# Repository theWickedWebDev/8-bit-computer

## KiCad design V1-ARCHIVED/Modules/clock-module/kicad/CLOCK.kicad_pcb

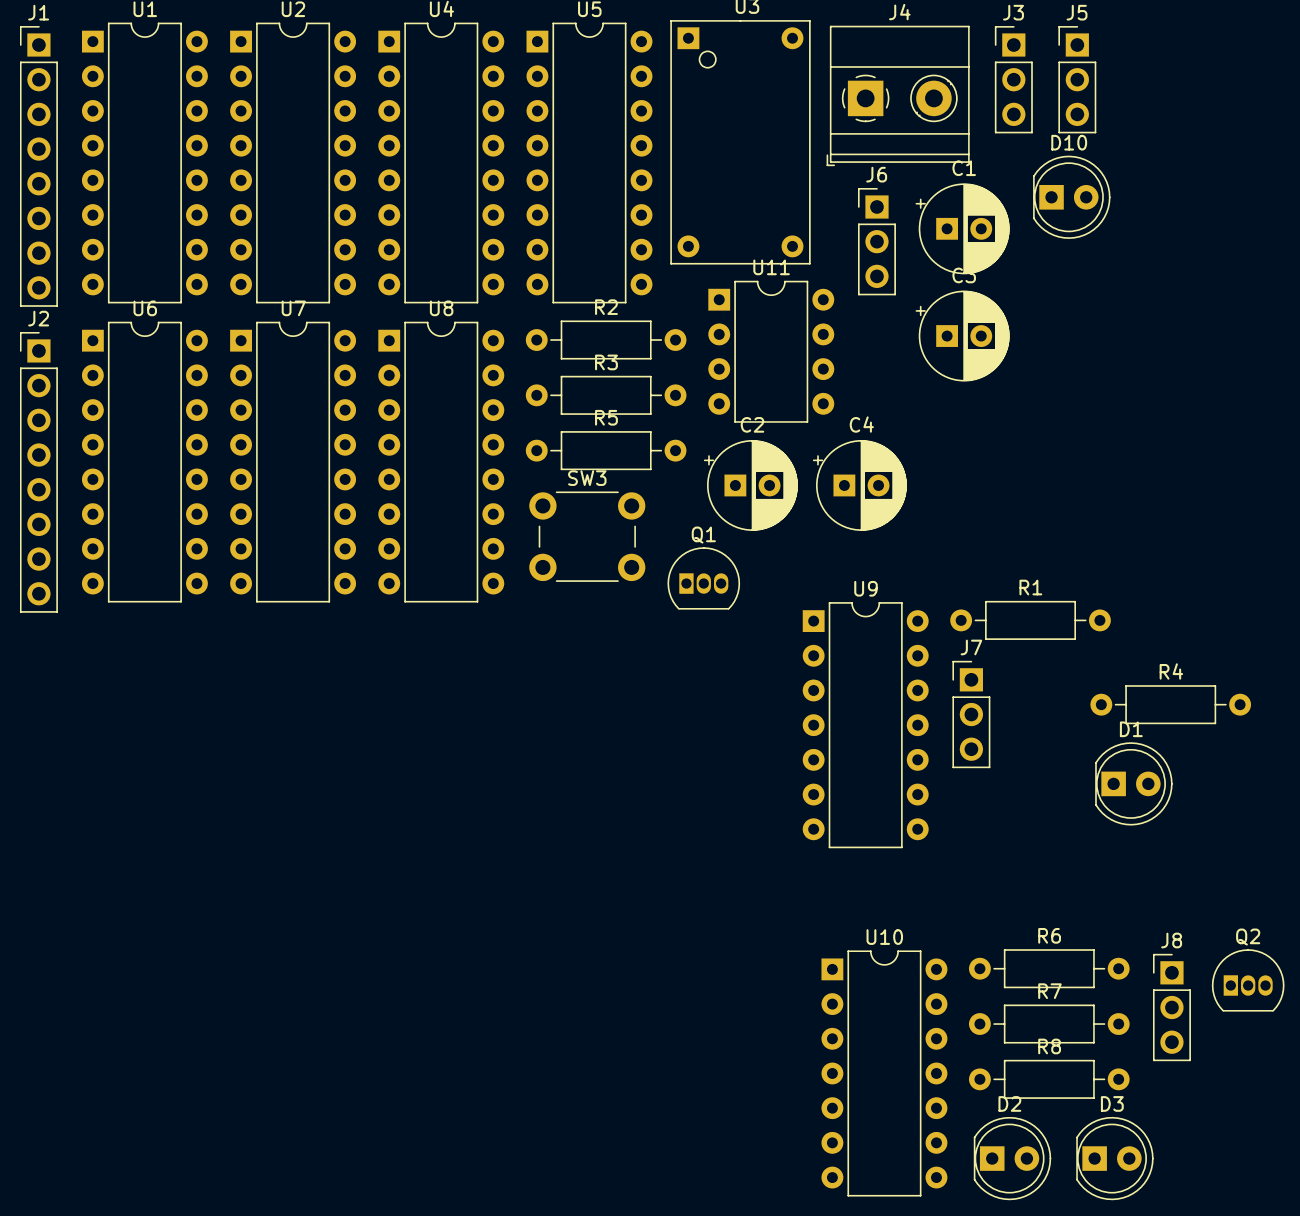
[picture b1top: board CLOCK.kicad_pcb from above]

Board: 4 copper layers, 38 parts (0 on the bottom side), 36 nets, no tracks yet.

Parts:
C1, C2, C3, C4: CP1; CP_Radial_D6.3mm_P2.50mm
D1, D2, D3, D10: LED; LED_D5.0mm
J1: Conn_01x03; PinHeader_1x08_P2.54mm_Vertical
J2: Conn_01x08; PinHeader_1x08_P2.54mm_Vertical
J3, J5, J6, J7, J8: Conn_01x03; PinHeader_1x03_P2.54mm_Vertical
J4: Screw_Terminal_01x02; TerminalBlock_Phoenix_MKDS-1,5-2_1x02_P5.00mm_Horizontal
Q1, Q2: PN2222A; TO-92_Inline
R1, R2, R3, R4, R5, R6, R7, R8: R_Small_US; R_Axial_DIN0207_L6.3mm_D2.5mm_P10.16mm_Horizontal
SW3: SW_Push; SW_PUSH_6mm
U1, U2, U4, U6, U7, U8: 74LS193; DIP-16_W7.62mm
U3: 4-pin-crystal-1mhz; full-can-14pin
U5: 74LS251; DIP-16_W7.62mm
U9: 74LS08; DIP-14_W7.62mm
U10: 74LS32; DIP-14_W7.62mm
U11: LM555xN; DIP-8_W7.62mm

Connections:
1MHz_Pulse: U3.8, U4.5, U5.12
CLOCK_OUT: D10.2, J2.1, J2.2, J2.3, J2.4, J2.5, J2.6, J2.7, J2.8
GND: C1.2, C2.2, C3.2, C4.2, J3.3, J4.1, J5.3, J6.3, J7.1, J8.1, Q1.3, Q2.3, R4.2, R5.2, R6.2, R8.2, SW3.1, U1.1, U1.8, U1.9, U1.10, U1.14, U1.15, U2.1, U2.8, U2.9, U2.10, U2.14, U2.15, U3.7, U4.1, U4.8, U4.9, U4.10, U4.14, U4.15, U5.7, U5.8, U6.1, U6.8, U6.9, U6.10, U6.14, U6.15, U7.1, U7.8, U7.9, U7.10, U7.14, U7.15, U8.1, U8.8, U8.9, U8.10, U8.14, U8.15, U9.7, U10.7, U11.1
Monostable_Pulse: U9.5, U11.3
unnamed: C3.1, U11.5
unnamed: C4.1, R2.1, U11.6, U11.7
unnamed: D1.1, R4.1
unnamed: D1.2, J7.2, Q1.2, U9.4
unnamed: D2.1, R6.1
unnamed: D2.2, U9.8
unnamed: D3.1, R8.1
unnamed: D3.2, J8.2, Q2.2
unnamed: D10.1, R5.1
unnamed: J3.2, U5.11
unnamed: J5.2, U5.10
unnamed: J6.2, U5.9
unnamed: Q1.1, R1.2, U9.1
unnamed: Q2.1, R7.1, U9.9
unnamed: R3.2, SW3.2, U11.2
unnamed: U1.3, U5.14
unnamed: U1.5, U4.12
unnamed: U1.12, U2.5
unnamed: U2.12, U6.5
unnamed: U4.3, U5.13
unnamed: U5.1, U6.7
unnamed: U5.2, U7.3
unnamed: U5.3, U7.7
unnamed: U5.4, U8.3
unnamed: U5.5, U9.2
unnamed: U5.15, U6.6
unnamed: U6.12, U7.5
unnamed: U7.12, U8.5
unnamed: U9.3, U10.1
unnamed: U9.6, U10.2
unnamed: U9.10, U10.3
VCC: C1.1, C2.1, J3.1, J4.2, J5.1, J6.1, J7.3, J8.3, R1.1, R2.2, R3.1, R7.2, U1.4, U1.16, U2.4, U2.16, U3.14, U4.4, U4.16, U5.16, U6.4, U6.16, U7.4, U7.16, U8.4, U8.16, U9.14, U10.14, U11.8

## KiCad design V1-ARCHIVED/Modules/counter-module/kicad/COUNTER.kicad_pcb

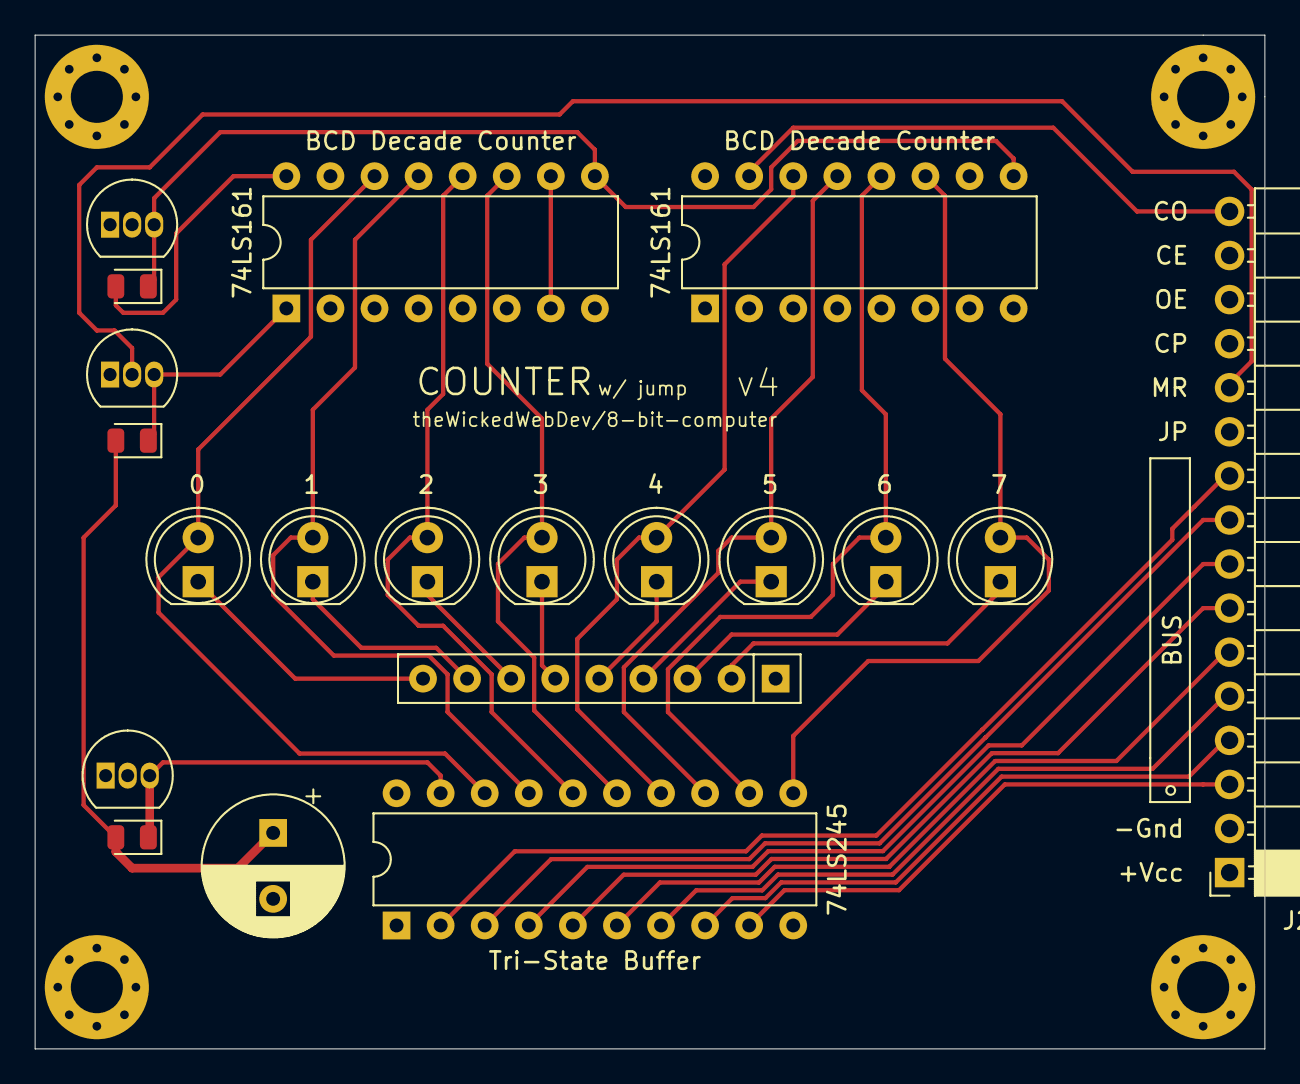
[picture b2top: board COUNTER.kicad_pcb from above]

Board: 4 copper layers, 70.9 x 58.4 mm, 20 parts (0 on the bottom side), 36 nets.

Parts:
C10: CP1; CP_Radial_D8.0mm_P3.80mm
D1, D2, D3, D4, D5, D6, D7, D8: LED; LED_D5.0mm
J22: Conn_01x16; PinSocket_1x16_P2.54mm_Horizontal
Q1, Q2, Q3: PN2222A; TO-92_Inline
R1, R2, R3: R_Small_US; LED_0805_2012Metric
RN1: R_Network08; R_Array_SIP9
U12, U14: 74LS161; DIP-16_W7.62mm
U47: 74LS245; DIP-20_W7.62mm

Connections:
!JUMP: Q1.3, R1.1, U12.9, U14.9
!OE: Q2.3, R2.1, U47.19
!RESET: Q3.3, R3.1, U12.1, U14.1
B0: D1.2, U14.14, U47.18
B1: D2.2, U14.13, U47.17
B2: D3.2, U14.12, U47.16
B3: D4.2, U14.11, U47.15
B4: D5.2, U12.14, U47.14
B5: D6.2, U12.13, U47.13
B6: D7.2, U12.12, U47.12
B7: D8.2, U12.11, U47.11
BUS_00: J22.3, U14.3, U47.9
BUS_01: J22.4, U14.4, U47.8
BUS_02: J22.5, U14.5, U47.7
BUS_03: J22.6, U14.6, U47.6
BUS_04: J22.7, U12.3, U47.5
BUS_05: J22.8, U12.4, U47.4
BUS_06: J22.9, U12.5, U47.3
BUS_07: J22.10, U12.6, U47.2
CARRY_OUT: J22.16, U12.15
CE: J22.15, U14.7, U14.10
CLOCK: J22.13, U12.2, U14.2
GND: C10.2, J22.2, Q1.1, Q2.1, Q3.1, RN1.1, U12.8, U14.8, U47.1, U47.10
JUMP: J22.11, Q1.2
unnamed: D1.1, RN1.9
unnamed: D2.1, RN1.8
unnamed: D3.1, RN1.7
unnamed: D4.1, RN1.6
unnamed: D5.1, RN1.5
unnamed: D6.1, RN1.4
unnamed: D7.1, RN1.3
unnamed: D8.1, RN1.2
unnamed: U12.10, U14.15
OE: J22.14, Q2.2
RESET: J22.12, Q3.2
VCC: C10.1, J22.1, R1.2, R2.2, R3.2, U12.7, U12.16, U14.16, U47.20

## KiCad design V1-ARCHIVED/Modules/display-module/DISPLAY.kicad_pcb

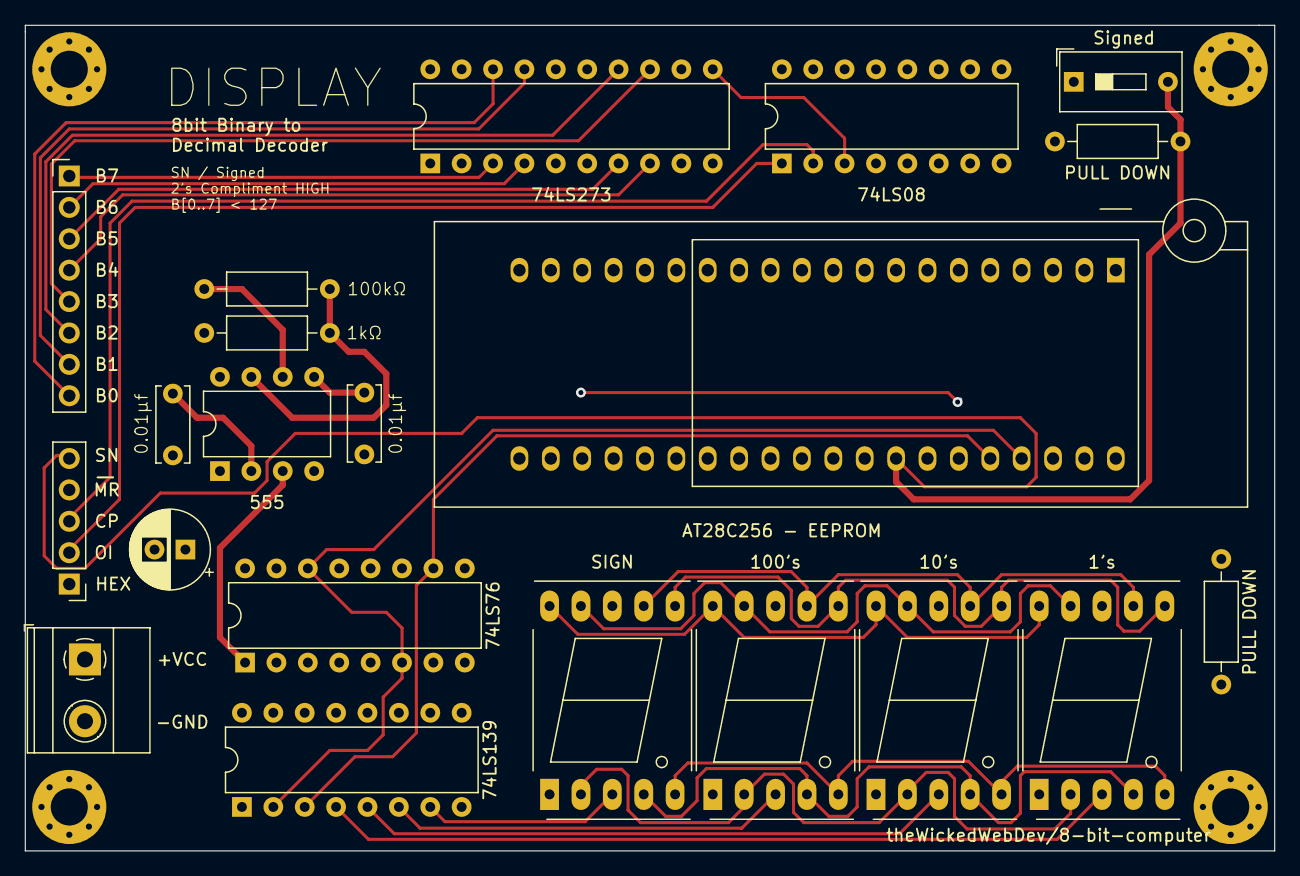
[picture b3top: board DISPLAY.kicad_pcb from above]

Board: 4 copper layers, 101.1 x 66.8 mm, 21 parts (0 on the bottom side), 42 nets.

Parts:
C16: CP1; CP_Radial_D6.3mm_P2.50mm
C133: CP; C_Disc_D6.0mm_W2.5mm_P5.00mm
C233: C; C_Disc_D6.0mm_W2.5mm_P5.00mm
J1: Screw_Terminal_01x02; TerminalBlock_Phoenix_MKDS-1,5-2_1x02_P5.00mm_Horizontal
J2: Conn_01x08; PinHeader_1x08_P2.54mm_Vertical
J3: Conn_01x05; PinHeader_1x05_P2.54mm_Vertical
R1, R2, R1452, R2123: R_US; R_Axial_DIN0207_L6.3mm_D2.5mm_P10.16mm_Horizontal
SW1: SW_SPST; SW_DIP_SPSTx01_Slide_9.78x4.72mm_W7.62mm_P2.54mm
U1, U4, U5, U6: HDSP-7503; 7SegmentLED_LTS6760_LTS6780
U2: 74LS08; DIP-16_W7.62mm
U3: 74LS273; DIP-20_W7.62mm
U9: AT28C256; DIP_Socket-40_W11.9_W12.7_W15.24_W17.78_W18.5_3M_240-1280-0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
U1555: NE55P; DIP-8_W7.62mm
U2444: 74LS76; DIP-16_W7.62mm
U4332: 74LS139; DIP-16_W7.62mm

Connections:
1_DISPLAY: U6.3, U6.8, U4332.4
10_DISPLAY: U5.3, U5.8, U4332.5
100_DISPLAY: U4.3, U4.8, U4332.6
A0: U9.25, U2444.6, U2444.14, U4332.2
A1: U9.24, U2444.10, U4332.3
A_SEG: U1.7, U4.7, U5.7, U6.7, U9.18
BUS0: J2.8, U3.18
BUS1: J2.7, U3.17
BUS2: J2.6, U3.14
BUS3: J2.5, U3.13
BUS4: J2.4, U3.8
BUS5: J2.3, U3.7
BUS6: J2.2, U3.4
BUS7: J2.1, U3.3
B_SEG: U1.6, U4.6, U5.6, U6.6, U9.17
CLOCK: J3.3, U2.2
C_SEG: U1.4, U4.4, U5.4, U6.4, U9.16
DP_SEG: U1.5, U4.5, U5.5, U6.5, U9.19
D_SEG: U1.2, U4.2, U5.2, U6.2, U9.15
E_SEG: U1.1, U4.1, U5.1, U6.1, U9.13
F_SEG: U1.9, U4.9, U5.9, U6.9, U9.12
GND: C16.2, C133.1, C233.2, J1.2, R1.1, R2.1, U2.7, U3.10, U9.1, U9.2, U9.14, U9.20, U9.22, U9.26, U1555.1, U2444.13, U4332.1, U4332.8
G_SEG: U1.10, U4.10, U5.10, U6.10, U9.11
HEX: J3.1, R2.2, U9.23
unnamed: C133.2, R1452.2, U1555.2, U1555.6
unnamed: C233.1, U1555.5
unnamed: R1452.1, R2123.1, U1555.7
unnamed: U2.3, U3.11
unnamed: U3.2, U9.3
unnamed: U3.5, U9.4
unnamed: U3.6, U9.5
unnamed: U3.9, U9.6
unnamed: U3.12, U9.7
unnamed: U3.15, U9.8
unnamed: U3.16, U9.9
unnamed: U3.19, U9.10
OI: J3.2, U2.1
RATE: U1555.3, U2444.1
RST: J3.4, U3.1
SIGNED: J3.5, R1.2, SW1.2, U9.21
SIGN_DISPLAY: U1.3, U1.8, U4332.7
VCC: C16.1, J1.1, R2123.2, SW1.1, U2.14, U3.20, U9.27, U9.28, U1555.8, U2444.2, U2444.3, U2444.4, U2444.5, U2444.7, U2444.8, U2444.9, U2444.12, U2444.16, U4332.16

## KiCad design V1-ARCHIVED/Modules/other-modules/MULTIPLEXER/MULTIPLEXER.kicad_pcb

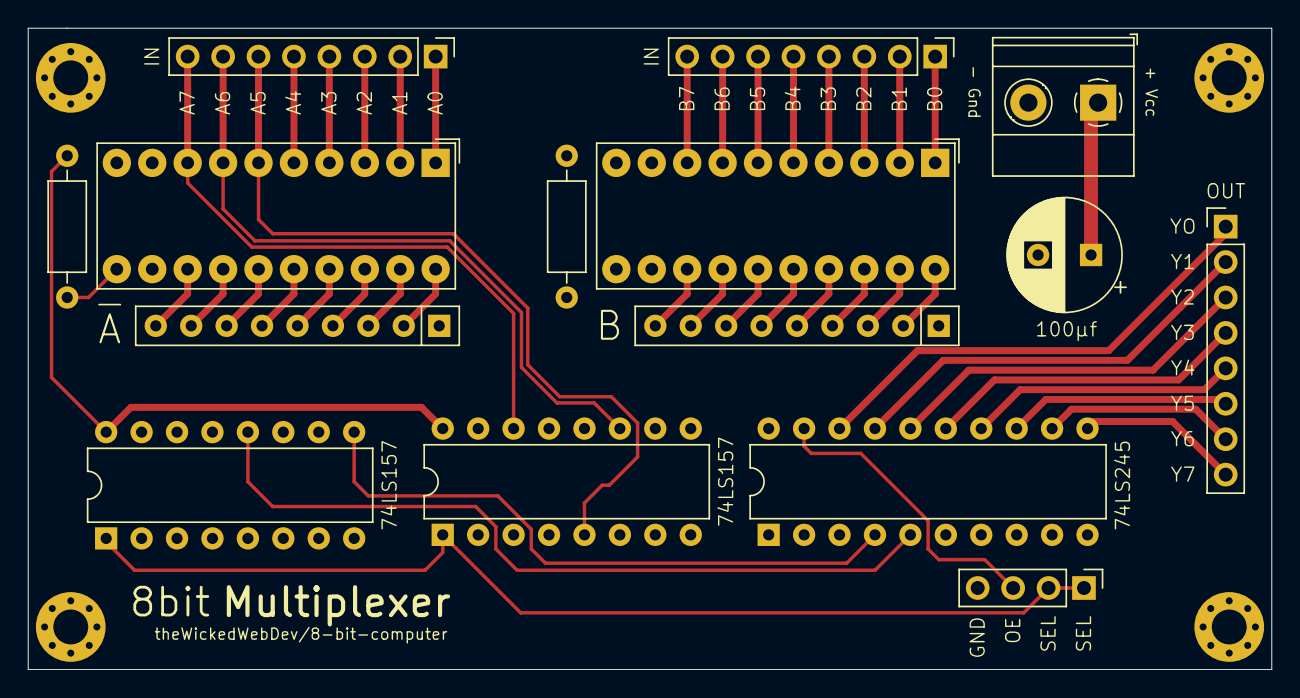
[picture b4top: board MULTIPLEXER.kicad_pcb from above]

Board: 4 copper layers, 89.2 x 46.0 mm, 15 parts (0 on the bottom side), 54 nets.

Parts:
BAR1, BAR2: HDSP-4830_2; HDSP-4830
C1: CP_Small; CP_Radial_D8.0mm_P3.80mm
J1: Screw_Terminal_01x02; TerminalBlock_Phoenix_MKDS-1,5-2_1x02_P5.00mm_Horizontal
J3: Conn_01x04; PinHeader_1x04_P2.54mm_Vertical
J4, J5, J6: Conn_01x08; PinHeader_1x08_P2.54mm_Vertical
R1, R3: R_Small_US; R_Axial_DIN0207_L6.3mm_D2.5mm_P10.16mm_Horizontal
RN1, RN2: R_Network08_US; R_Array_SIP9
U1, U2: 74LS157; DIP-16_W7.62mm
U3: 74LS245; DIP-20_W7.62mm

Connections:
A0: BAR1.1, J4.1, U1.2
A1: BAR1.2, J4.2, U1.5
A2: BAR1.3, J4.3, U1.11
A3: BAR1.4, J4.4, U1.14
A4: BAR1.5, J4.5, U2.2
A5: BAR1.6, J4.6, U2.5
A6: BAR1.7, J4.7, U2.11
A7: BAR1.8, J4.8, U2.14
B0: BAR2.1, J5.1, U1.3
B1: BAR2.2, J5.2, U1.6
B2: BAR2.3, J5.3, U1.10
B3: BAR2.4, J5.4, U1.13
B4: BAR2.5, J5.5, U2.3
B5: BAR2.6, J5.6, U2.6
B6: BAR2.7, J5.7, U2.10
B7: BAR2.8, J5.8, U2.13
GND: C1.2, J1.2, R3.1, RN1.1, RN2.1, U1.8, U1.15, U2.8, U2.15, U3.10
unnamed: BAR1.11, R1.2
unnamed: BAR1.13, RN1.9
unnamed: BAR1.14, RN1.8
unnamed: BAR1.15, RN1.7
unnamed: BAR1.16, RN1.6
unnamed: BAR1.17, RN1.5
unnamed: BAR1.18, RN1.4
unnamed: BAR1.19, RN1.3
unnamed: BAR1.20, RN1.2
unnamed: BAR2.11, R3.2
unnamed: BAR2.13, RN2.9
unnamed: BAR2.14, RN2.8
unnamed: BAR2.15, RN2.7
unnamed: BAR2.16, RN2.6
unnamed: BAR2.17, RN2.5
unnamed: BAR2.18, RN2.4
unnamed: BAR2.19, RN2.3
unnamed: BAR2.20, RN2.2
OE: J3.3, U3.19
SELECT: BAR1.10, BAR2.10, J3.1, J3.2, U1.1, U2.1
VCC: C1.1, J1.1, R1.1, U1.16, U2.16, U3.1, U3.20
Y0: J6.1, U3.18
Y1: J6.2, U3.17
Y2: J6.3, U3.16
Y3: J6.4, U3.15
Y4: J6.5, U3.14
Y5: J6.6, U3.13
Y6: J6.7, U3.12
Y7: J6.8, U3.11
Z0: U1.4, U3.2
Z1: U1.7, U3.3
Z2: U1.9, U3.4
Z3: U1.12, U3.5
Z4: U2.4, U3.6
Z5: U2.7, U3.7
Z6: U2.9, U3.8
Z7: U2.12, U3.9

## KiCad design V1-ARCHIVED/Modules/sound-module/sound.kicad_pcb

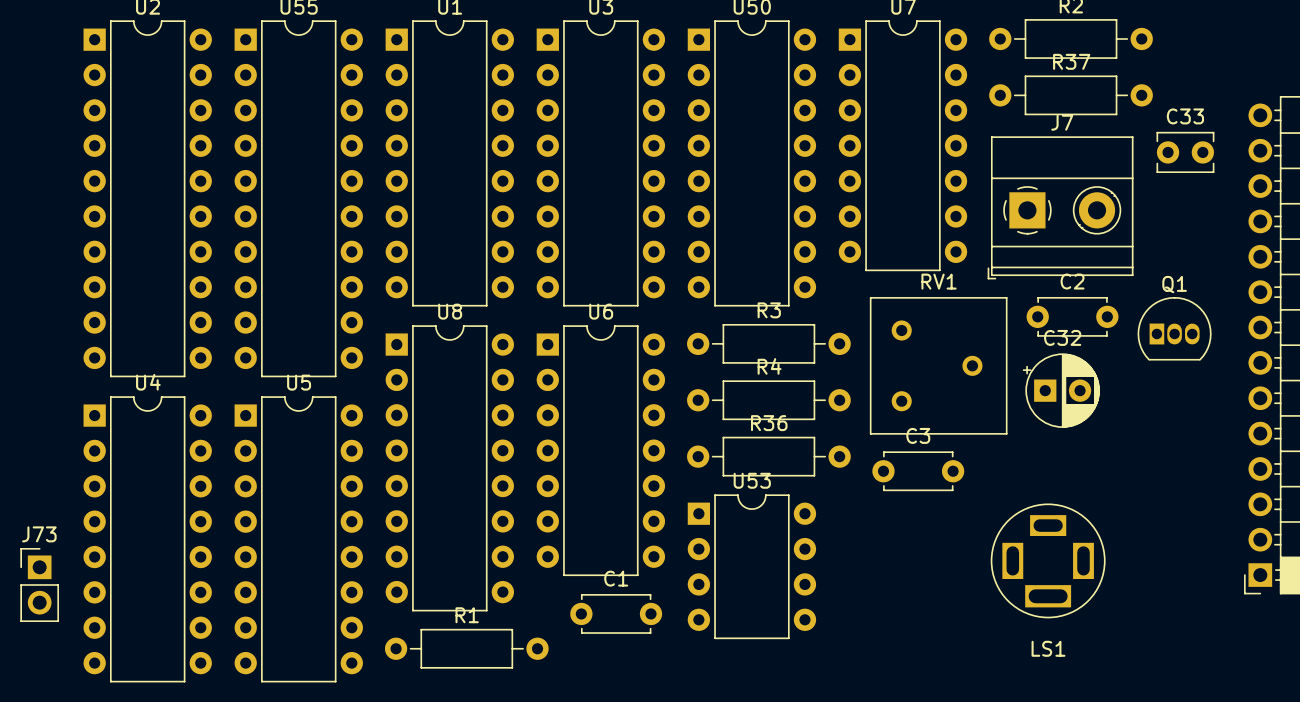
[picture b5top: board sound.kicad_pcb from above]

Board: 4 copper layers, 28 parts (0 on the bottom side), 44 nets, no tracks yet.

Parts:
C1, C2, C3: C; C_Disc_D4.7mm_W2.5mm_P5.00mm
C32: CP1_Small; CP_Radial_D5.0mm_P2.50mm
C33: C; C_Disc_D3.8mm_W2.6mm_P2.50mm
J7: Screw_Terminal_01x02; TerminalBlock_Phoenix_MKDS-1,5-2_1x02_P5.00mm_Horizontal
J69: Conn_01x14; PinSocket_1x14_P2.54mm_Horizontal
J73: Conn_01x02; PinHeader_1x02_P2.54mm_Vertical
LS1: Speaker; 3.5mm_Audio_Jack-STEPHEN
Q1: PN2222A; TO-92_Inline
R1, R2, R3, R4, R36, R37: R_Small_US; R_Axial_DIN0207_L6.3mm_D2.5mm_P10.16mm_Horizontal
RV1: R_POT_TRIM_US; Potentiometer_Bourns_3386F_Vertical
U1, U3, U4, U5: 74LS193; DIP-16_W7.62mm
U2, U55: 74LS273; DIP-20_W7.62mm
U6: 74LS04; DIP-14_W7.62mm
U7: 4073; DIP-14_W7.62mm
U8: 4072; DIP-16_W7.62mm
U50: CD4052B; DIP-16_W7.62mm
U53: LM555xN; DIP-8_W7.62mm

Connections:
BUS_00: J69.5, U55.3
BUS_01: J69.6, U55.4
BUS_02: J69.7, U55.7
BUS_03: J69.8, U55.8
BUS_04: J69.9, U55.13
BUS_05: J69.10, U55.14
BUS_06: J69.11, U55.17
BUS_07: J69.12, U55.18
GND: C2.1, C3.2, C32.2, C33.1, J69.14, Q1.1, R2.1, RV1.3, U1.8, U1.14, U2.10, U3.1, U3.8, U3.9, U3.10, U3.14, U3.15, U4.8, U4.14, U5.8, U5.14, U6.7, U7.7, U8.5, U8.7, U50.6, U50.7, U50.8, U53.1, U55.10
unnamed: C1.1, Q1.2, R1.1
unnamed: C2.2, R3.1, R4.1
unnamed: C3.1, R4.2, U7.5
unnamed: C33.2, R36.1, U53.2, U53.6
unnamed: J7.1, J73.1, LS1.R1, LS1.R2, RV1.2
unnamed: R36.2, R37.2, U53.7
unnamed: U1.2, U50.15
unnamed: U1.3, U50.11
unnamed: U1.5, U3.11, U3.13, U4.11, U5.11
unnamed: U1.6, U50.14
unnamed: U1.7, U50.12
unnamed: U3.4, U4.13
unnamed: U4.1, U55.15
unnamed: U4.4, U5.13
unnamed: U4.9, U55.19
unnamed: U4.10, U55.16
unnamed: U4.15, U55.12
unnamed: U5.1, U55.5
unnamed: U5.4, U53.3
unnamed: U5.9, U55.9
unnamed: U5.10, U55.6
unnamed: U5.15, U55.2
unnamed: U6.2, U7.1, U7.11
unnamed: U6.4, U7.2, U7.4
unnamed: U7.6, U8.3
unnamed: U7.9, U8.2
unnamed: U7.10, U8.4
SAWTOOTH_OUT: Q1.3, R2.2, U7.13
SET_META: J69.3, U2.11
SET_NOTE: J69.4, U55.11
SPEAKER: J7.2, J69.1, J73.2, LS1.S, LS1.T, U8.1
SQUARE_OUT: C1.2, R3.2, U7.8, U50.13
VCC: C32.1, J69.13, R1.2, R37.1, U1.4, U1.11, U1.16, U2.1, U2.20, U3.5, U3.16, U4.5, U4.16, U5.5, U5.16, U6.14, U7.14, U8.14, U50.16, U53.4, U53.5, U53.8, U55.1, U55.20
VOICE_00: U2.5, U6.1, U7.3
VOICE_01: U2.2, U6.3, U7.12

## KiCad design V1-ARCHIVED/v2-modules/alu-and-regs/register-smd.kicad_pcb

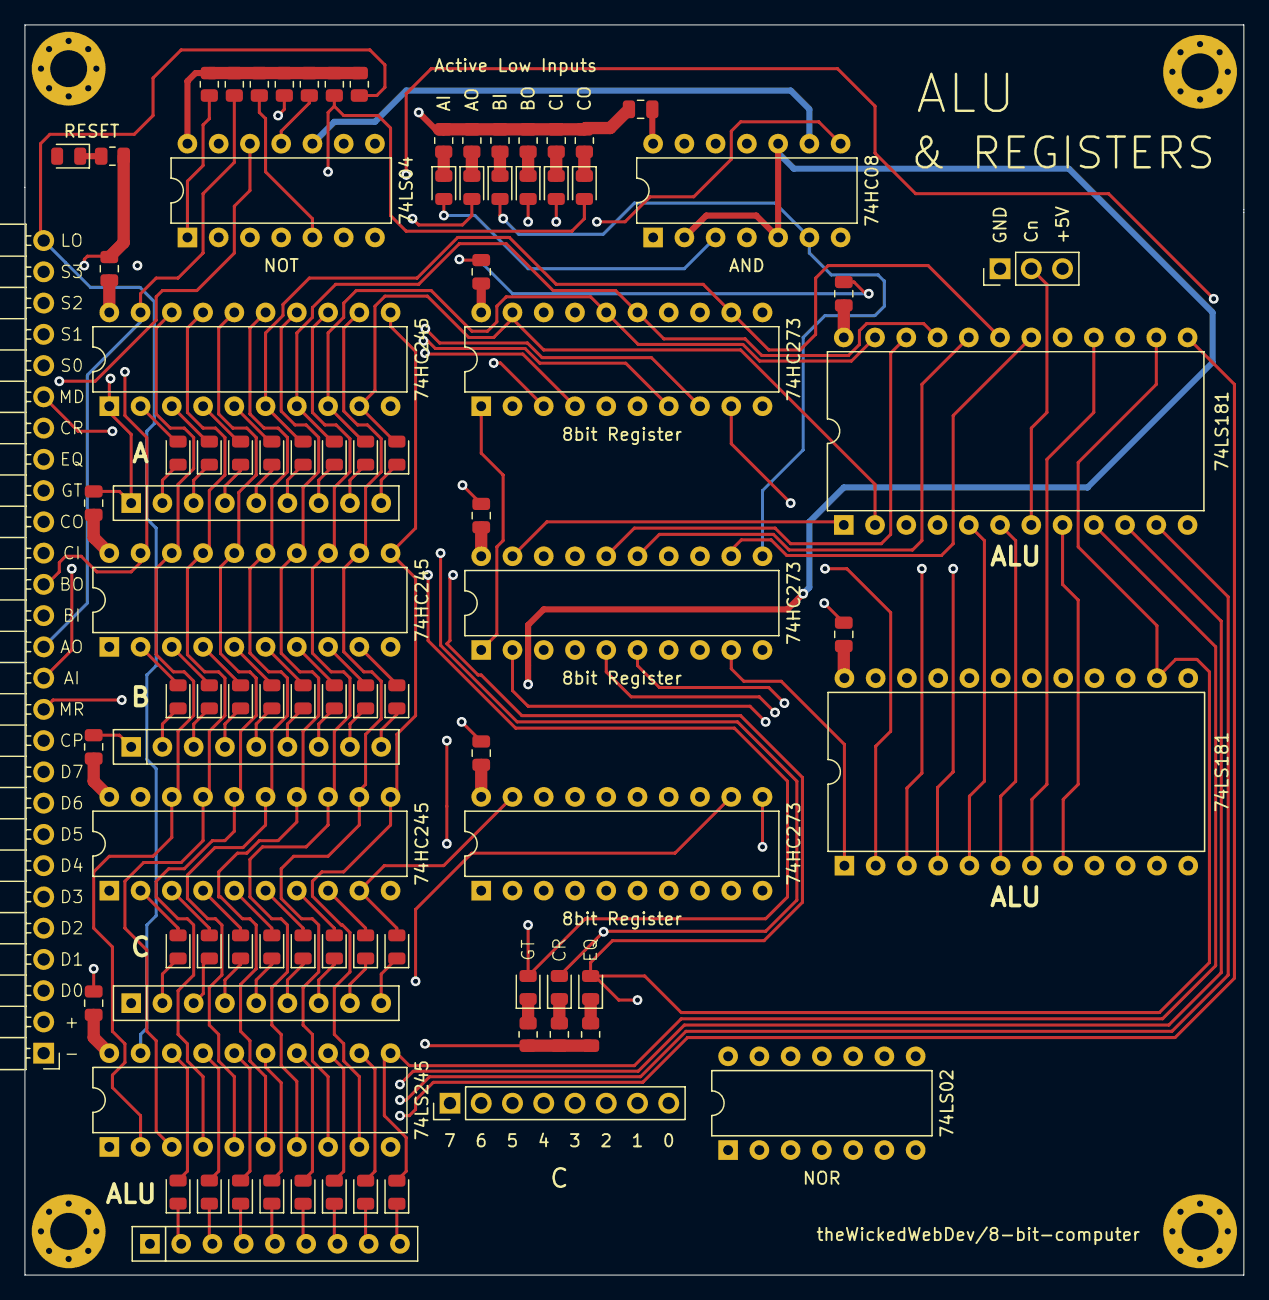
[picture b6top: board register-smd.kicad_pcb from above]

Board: 4 copper layers, 99.1 x 101.6 mm, 88 parts (0 on the bottom side), 110 nets.

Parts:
C1, C2, C3, C4, C5, C6, C7, C8, C9, C10: CP1; C_0805_2012Metric
D1, D2, D3, D4, D5, D6, D7, D8, D9, D10, D11, D12, D13, D14, D15, D16, D17, D18, D19, D20, D21, D22, D23, D24, D25, D26, D27, D28, D29, D30, D31, D32, D33, D34, D35, D36, D37, D38, D39, D40, D41, D42: LED; LED_0805_2012Metric
J1: Conn_01x27; PinHeader_1x27_P2.54mm_Horizontal
J2: Conn_01x08; PinHeader_1x08_P2.54mm_Vertical
J3: Conn_01x03; PinHeader_1x03_P2.54mm_Vertical
R1, R2, R3, R4, R5, R6, R7, R8, R9, R10, R11, R12, R13, R14, R15, R16, R17: R_Small_US; R_0805_2012Metric
RN1, RN2, RN3, RN4: R_Network08; R_Array_SIP9
U1: 74HC08; DIP-14_W7.62mm
U2: 74LS04; DIP-14_W7.62mm
U3, U4, U5: 74HC273; DIP-20_W7.62mm
U6, U7, U8: 74HC245; DIP-20_W7.62mm
U9, U10: 74LS181; DIP-24_W15.24mm
U12: 74LS02; DIP-14_W7.62mm
U13: 74LS245; DIP-20_W7.62mm

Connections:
+5V_IN: C1.1, C2.1, C3.1, C4.1, C5.1, C6.1, C7.1, C8.1, C9.1, C10.1, J1.2, J3.3, R1.1, R2.1, R3.1, R4.2, R5.2, R6.2, R12.1, U1.14, U2.14, U3.20, U4.20, U5.20, U6.20, U7.20, U8.20, U9.24, U10.24, U12.14, U13.20
-5V_IN: C1.2, C2.2, C3.2, C4.2, C5.2, C6.2, C7.2, C8.2, C9.2, C10.2, J1.1, J3.1, R7.2, R8.2, R9.2, R10.2, R11.2, R13.2, R14.2, R15.2, R16.2, R17.2, RN1.1, RN2.1, RN3.1, RN4.1, U1.7, U2.7, U3.10, U4.10, U5.10, U6.1, U6.10, U7.1, U7.10, U8.1, U8.10, U9.12, U10.12, U12.7, U13.1, U13.10
/A0: D12.2, U3.19, U6.9, U9.2
/A1: D13.2, U3.16, U6.8, U9.23
/A2: D14.2, U3.15, U6.7, U9.21
/A3: D15.2, U3.12, U6.6, U9.19
/A4: D16.2, U3.9, U6.5, U10.2
/A5: D17.2, U3.6, U6.4, U10.23
/A6: D18.2, U3.5, U6.3, U10.21
/A7: D19.2, U3.2, U6.2, U10.19
/ALU0: D1.2, U9.9, U13.11
/ALU1: D2.2, U9.10, U13.12
/ALU2: D3.2, U9.11, U13.13
/ALU3: D4.2, U9.13, U13.14
/ALU4: D5.2, U10.9, U13.15
/ALU5: D6.2, U10.10, U13.16
/ALU6: D7.2, U10.11, U13.17
/ALU7: D8.2, U10.13, U13.18
/A_IN_CP: D20.2, U1.3, U3.11
/B0: D22.2, U4.19, U7.9, U9.1
/B1: D23.2, U4.16, U7.8, U9.22
/B2: D24.2, U4.15, U7.7, U9.20
/B3: D25.2, U4.12, U7.6, U9.18
/B4: D26.2, U4.9, U7.5, U10.1
/B5: D27.2, U4.6, U7.4, U10.22
/B6: D28.2, U4.5, U7.3, U10.20
/B7: D29.2, U4.2, U7.2, U10.18
/B_IN_CP: D30.2, U1.6, U4.11
/C0: D32.2, J2.8, U5.19, U8.9
/C1: D33.2, J2.7, U5.16, U8.8
/C2: D34.2, J2.6, U5.15, U8.7
/C3: D35.2, J2.5, U5.12, U8.6
/C4: D36.2, J2.4, U5.9, U8.5
/C5: D37.2, J2.3, U5.6, U8.4
/C6: D38.2, J2.2, U5.5, U8.3
/C7: D39.2, J2.1, U5.2, U8.2
/C_IN_CP: D40.2, U1.8, U5.11
/Cn: J3.2, U9.7
AI: J1.13, R1.2, U2.1
ALU_MODE: J1.22, U9.8, U10.8
ALU_OUT: J1.27, R12.2, U13.19
ALU_S0: J1.23, U9.6, U10.6
ALU_S1: J1.24, U9.5, U10.5
ALU_S2: J1.25, U9.4, U10.4
ALU_S3: J1.26, U9.3, U10.3
AO: D21.2, J1.14, R4.1, U6.19
A_EQ_B: D10.2, J1.20, U9.14, U10.14, U12.6
A_GT_B: D11.2, J1.19, U12.4
BI: J1.15, R2.2, U2.5
BO: D31.2, J1.16, R5.1, U7.19
BUS_00: J1.3, U3.18, U4.18, U5.18, U6.11, U7.11, U8.11, U13.9
BUS_01: J1.4, U3.17, U4.17, U5.17, U6.12, U7.12, U8.12, U13.8
BUS_02: J1.5, U3.14, U4.14, U5.14, U6.13, U7.13, U8.13, U13.7
BUS_03: J1.6, U3.13, U4.13, U5.13, U6.14, U7.14, U8.14, U13.6
BUS_04: J1.7, U3.8, U4.8, U5.8, U6.15, U7.15, U8.15, U13.5
BUS_05: J1.8, U3.7, U4.7, U5.7, U6.16, U7.16, U8.16, U13.4
BUS_06: J1.9, U3.4, U4.4, U5.4, U6.17, U7.17, U8.17, U13.3
BUS_07: J1.10, U3.3, U4.3, U5.3, U6.18, U7.18, U8.18, U13.2
CARRY: D9.2, J1.21, U2.12, U12.5
CI: J1.17, R3.2, U2.11
CLOCK: J1.11, U1.2, U1.5, U1.10
CO: D41.2, J1.18, R6.1, U8.19
unnamed: D1.1, RN1.9
unnamed: D2.1, RN1.8
unnamed: D3.1, RN1.7
unnamed: D4.1, RN1.6
unnamed: D5.1, RN1.5
unnamed: D6.1, RN1.4
unnamed: D7.1, RN1.3
unnamed: D8.1, RN1.2
unnamed: D9.1, R7.1
unnamed: D10.1, R8.1
unnamed: D11.1, R9.1
unnamed: D12.1, RN2.9
unnamed: D13.1, RN2.8
unnamed: D14.1, RN2.7
unnamed: D15.1, RN2.6
unnamed: D16.1, RN2.5
unnamed: D17.1, RN2.4
unnamed: D18.1, RN2.3
unnamed: D19.1, RN2.2
unnamed: D20.1, R10.1
unnamed: D21.1, R11.1
unnamed: D22.1, RN3.9
unnamed: D23.1, RN3.8
unnamed: D24.1, RN3.7
unnamed: D25.1, RN3.6
unnamed: D26.1, RN3.5
unnamed: D27.1, RN3.4
unnamed: D28.1, RN3.3
unnamed: D29.1, RN3.2
unnamed: D30.1, R13.1
unnamed: D31.1, R14.1
unnamed: D32.1, RN4.9
unnamed: D33.1, RN4.8
unnamed: D34.1, RN4.7
unnamed: D35.1, RN4.6
unnamed: D36.1, RN4.5
unnamed: D37.1, RN4.4
unnamed: D38.1, RN4.3
unnamed: D39.1, RN4.2
unnamed: D40.1, R15.1
unnamed: D41.1, R16.1
unnamed: D42.1, R17.1
unnamed: U1.1, U2.2
unnamed: U1.4, U2.6
unnamed: U1.9, U2.10
unnamed: U9.16, U10.7
unnamed: U2.13, U10.16
RESET: J1.12, U3.1, U4.1, U5.1

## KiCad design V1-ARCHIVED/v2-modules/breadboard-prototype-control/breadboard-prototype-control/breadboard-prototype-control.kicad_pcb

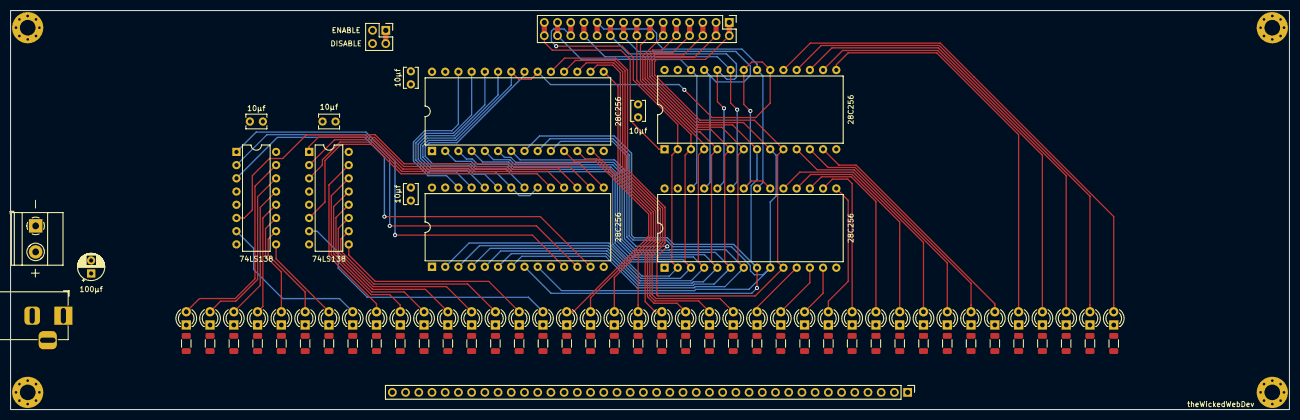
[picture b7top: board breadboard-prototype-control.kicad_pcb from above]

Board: 2 copper layers, 245.9 x 76.7 mm, 97 parts (0 on the bottom side), 107 nets.

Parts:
C1: CP1_Small; CP_Radial_D5.0mm_P2.50mm
C2, C3, C4, C6, C7: CP1_Small; C_Disc_D3.8mm_W2.6mm_P2.50mm
D1, D2, D3, D4, D5, D6, D7, D8, D9, D10, D11, D12, D13, D14, D15, D16, D17, D18, D19, D20, D21, D22, D23, D24, D25, D26, D27, D28, D29, D30, D31, D32, D33, D34, D35, D36, D37, D38, D39, D40: LED; LED_D3.0mm
J1: Conn_02x02_Top_Bottom; PinHeader_2x02_P2.54mm_Vertical
J2: Conn_02x15_Top_Bottom; PinHeader_2x15_P2.54mm_Vertical
J3: Conn_02x20_Top_Bottom; PinHeader_1x40_P2.54mm_Vertical
J5: Screw_Terminal_01x02; TerminalBlock_Phoenix_MKDS-1,5-2_1x02_P5.00mm_Horizontal
J17: Barrel_Jack_MountingPin; BarrelJack_Horizontal
R1, R2, R3, R4, R5, R6, R7, R8, R9, R10, R11, R12, R13, R14, R15, R16, R17, R18, R19, R20, R21, R22, R23, R24, R25, R26, R27, R28, R29, R30, R31, R32, R33, R34, R35, R36, R37, R38, R39, R40: R_Small_US; R_1206_3216Metric
U1, U2, U3, U4: 28C256; DIP-28_W15.24mm
U5, U6: 74LS138; DIP-16_W7.62mm

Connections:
CONTROL_00: D17.2, J3.24, U2.11
CONTROL_01: D18.2, J3.23, U2.12
CONTROL_02: D19.2, J3.22, U2.13
CONTROL_03: D20.2, J3.21, U2.15
CONTROL_04: D21.2, J3.20, U2.16
CONTROL_05: D22.2, J3.19, U2.17
CONTROL_06: D23.2, J3.18, U2.18
CONTROL_07: D24.2, J3.17, U2.19
CONTROL_08: D25.2, J3.16, U3.11
CONTROL_09: D26.2, J3.15, U3.12
CONTROL_10: D27.2, J3.14, U3.13
CONTROL_11: D28.2, J3.13, U3.15
CONTROL_12: D29.2, J3.12, U3.16
CONTROL_13: D30.2, J3.11, U3.17
CONTROL_14: D31.2, J3.10, U3.18
CONTROL_15: D32.2, J3.9, U3.19
CONTROL_16: D33.2, J3.8, U1.11
CONTROL_17: D34.2, J3.7, U1.12
CONTROL_18: D35.2, J3.6, U1.13
CONTROL_19: D36.2, J3.5, U1.15
CONTROL_20: D37.2, J3.4, U1.16
CONTROL_21: D38.2, J3.3, U1.17
CONTROL_22: D39.2, J3.2, U1.18
CONTROL_23: D40.2, J3.1, U1.19
CONTROL_IN_00: D9.2, J3.32, U6.15
CONTROL_IN_01: D10.2, J3.31, U6.14
CONTROL_IN_02: D11.2, J3.30, U6.13
CONTROL_IN_03: D12.2, J3.29, U6.12
CONTROL_IN_04: D13.2, J3.28, U6.11
CONTROL_IN_05: D14.2, J3.27, U6.10
CONTROL_IN_06: D15.2, J3.26, U6.9
CONTROL_IN_07: D16.2, J3.25, U6.7
CONTROL_OUT_00: D1.2, J3.40, U5.15
CONTROL_OUT_01: D2.2, J3.39, U5.14
CONTROL_OUT_02: D3.2, J3.38, U5.13
CONTROL_OUT_03: D4.2, J3.37, U5.12
CONTROL_OUT_04: D5.2, J3.36, U5.11
CONTROL_OUT_05: D6.2, J3.35, U5.10
CONTROL_OUT_06: D7.2, J3.34, U5.9
CONTROL_OUT_07: D8.2, J3.33, U5.7
ENABLE_MICROCODE: J1.1, J1.2, U1.20, U1.22, U2.20, U2.22, U3.20, U3.22, U4.20, U4.22
FLAG_00: J2.7, J2.8, U1.7, U2.7, U3.7, U4.7
FLAG_01: J2.9, J2.10, U1.6, U2.6, U3.6, U4.6
FLAG_03: J2.11, J2.12, U1.5, U2.5, U3.5, U4.5
FLAG_04: J2.13, J2.14, U1.4, U2.4, U3.4, U4.4
GND: C1.2, C2.2, C3.2, C4.2, C6.2, C7.2, J1.3, J5.1, J17.2, R1.2, R2.2, R3.2, R4.2, R5.2, R6.2, R7.2, R8.2, R9.2, R10.2, R11.2, R12.2, R13.2, R14.2, R15.2, R16.2, R17.2, R18.2, R19.2, R20.2, R21.2, R22.2, R23.2, R24.2, R25.2, R26.2, R27.2, R28.2, R29.2, R30.2, R31.2, R32.2, R33.2, R34.2, R35.2, R36.2, R37.2, R38.2, R39.2, R40.2, U1.14, U2.14, U3.14, U4.14, U5.4, U5.5, U5.8, U6.8
INST_00: J2.15, J2.16, U1.3, U2.3, U3.3, U4.3
INST_01: J2.17, J2.18, U1.25, U2.25, U3.25, U4.25
INST_02: J2.19, J2.20, U1.24, U2.24, U3.24, U4.24
INST_03: J2.21, J2.22, U1.21, U2.21, U3.21, U4.21
INST_04: J2.23, J2.24, U1.23, U2.23, U3.23, U4.23
INST_05: J2.25, J2.26, U1.2, U2.2, U3.2, U4.2
INST_06: J2.27, J2.28, U1.26, U2.26, U3.26, U4.26
INST_07: J2.29, J2.30, U1.1, U2.1, U3.1, U4.1
unnamed: D1.1, R1.1
unnamed: D2.1, R2.1
unnamed: D3.1, R3.1
unnamed: D4.1, R4.1
unnamed: D5.1, R5.1
unnamed: D6.1, R6.1
unnamed: D7.1, R7.1
unnamed: D8.1, R8.1
unnamed: D9.1, R9.1
unnamed: D10.1, R10.1
unnamed: D11.1, R11.1
unnamed: D12.1, R12.1
unnamed: D13.1, R13.1
unnamed: D14.1, R14.1
unnamed: D15.1, R15.1
unnamed: D16.1, R16.1
unnamed: D17.1, R17.1
unnamed: D18.1, R18.1
unnamed: D19.1, R19.1
unnamed: D20.1, R20.1
unnamed: D21.1, R21.1
unnamed: D22.1, R22.1
unnamed: D23.1, R23.1
unnamed: D24.1, R24.1
unnamed: D25.1, R25.1
unnamed: D26.1, R26.1
unnamed: D27.1, R27.1
unnamed: D28.1, R28.1
unnamed: D29.1, R29.1
unnamed: D30.1, R30.1
unnamed: D31.1, R31.1
unnamed: D32.1, R32.1
unnamed: D33.1, R33.1
unnamed: D34.1, R34.1
unnamed: D35.1, R35.1
unnamed: D36.1, R36.1
unnamed: D37.1, R37.1
unnamed: D38.1, R38.1
unnamed: D39.1, R39.1
unnamed: D40.1, R40.1
unnamed: U4.11, U5.1
unnamed: U4.12, U5.2
unnamed: U4.13, U5.3
unnamed: U4.15, U5.6
unnamed: U4.16, U6.1
unnamed: U4.17, U6.2
unnamed: U4.18, U6.3
unnamed: U4.19, U6.6
unnamed: U6.4, U6.5
STEP_00: J2.1, J2.2, U1.10, U2.10, U3.10, U4.10
STEP_01: J2.3, J2.4, U1.9, U2.9, U3.9, U4.9
STEP_02: J2.5, J2.6, U1.8, U2.8, U3.8, U4.8
VCC: C1.1, C2.1, C3.1, C4.1, C6.1, C7.1, J1.4, J5.2, J17.1, U1.27, U1.28, U2.27, U2.28, U3.27, U3.28, U4.27, U4.28, U5.16, U6.16
